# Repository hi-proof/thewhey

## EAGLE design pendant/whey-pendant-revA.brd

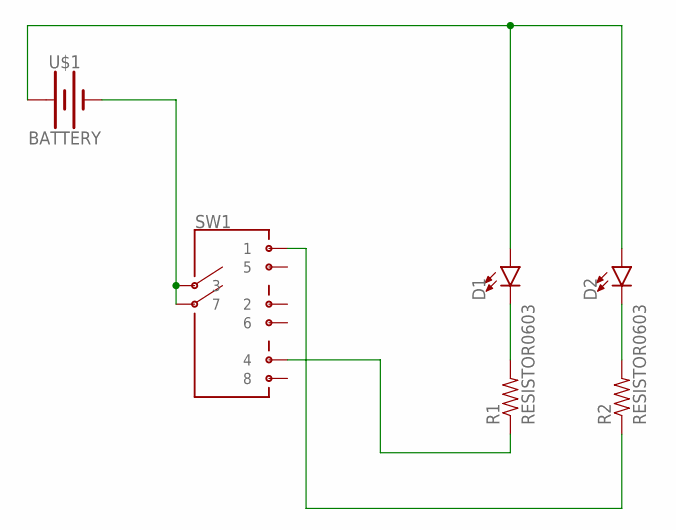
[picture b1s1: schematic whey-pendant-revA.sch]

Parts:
D1, D2: LED1206; LED-1206
R1, R2: RESISTOR0603; R0603
SW1: JS203011JCQN
U$1: BATTERY; COINCELL16

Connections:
unnamed: D1.A, D2.A, U$1.P$1 (+), U$1.P$2 (+)
unnamed: D1.C, R1.2
unnamed: D2.C, R2.2
unnamed: SW1.3, SW1.7, U$1.P$3 (-)
unnamed: R1.1, SW1.4
unnamed: R2.1, SW1.1

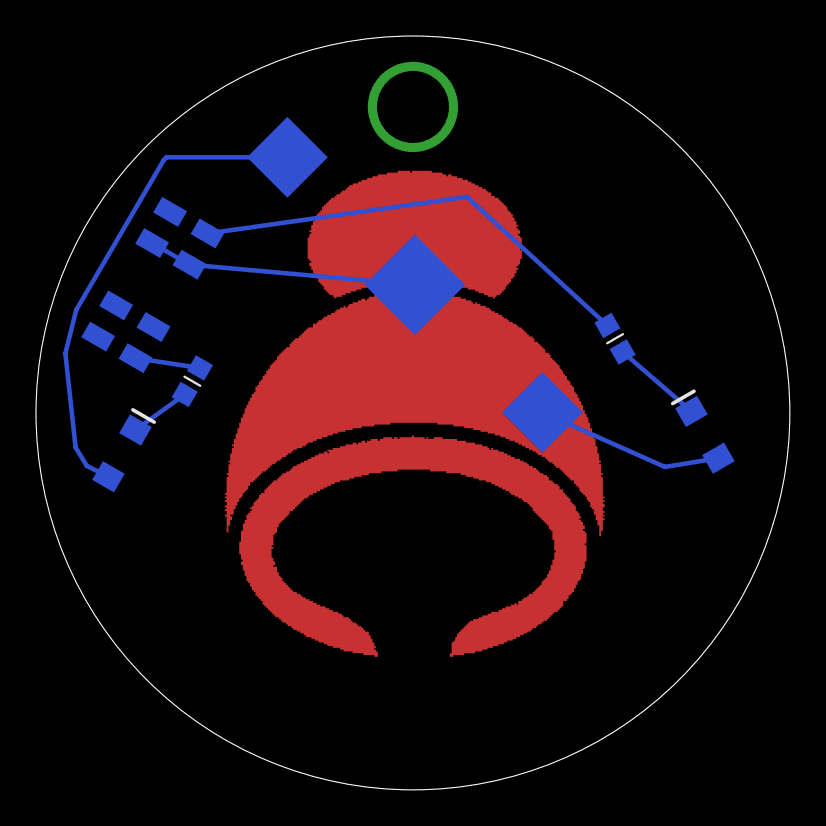
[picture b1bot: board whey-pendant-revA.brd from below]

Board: 2 copper layers, 41.9 x 41.9 mm, 6 parts (6 on the bottom side), 6 nets.

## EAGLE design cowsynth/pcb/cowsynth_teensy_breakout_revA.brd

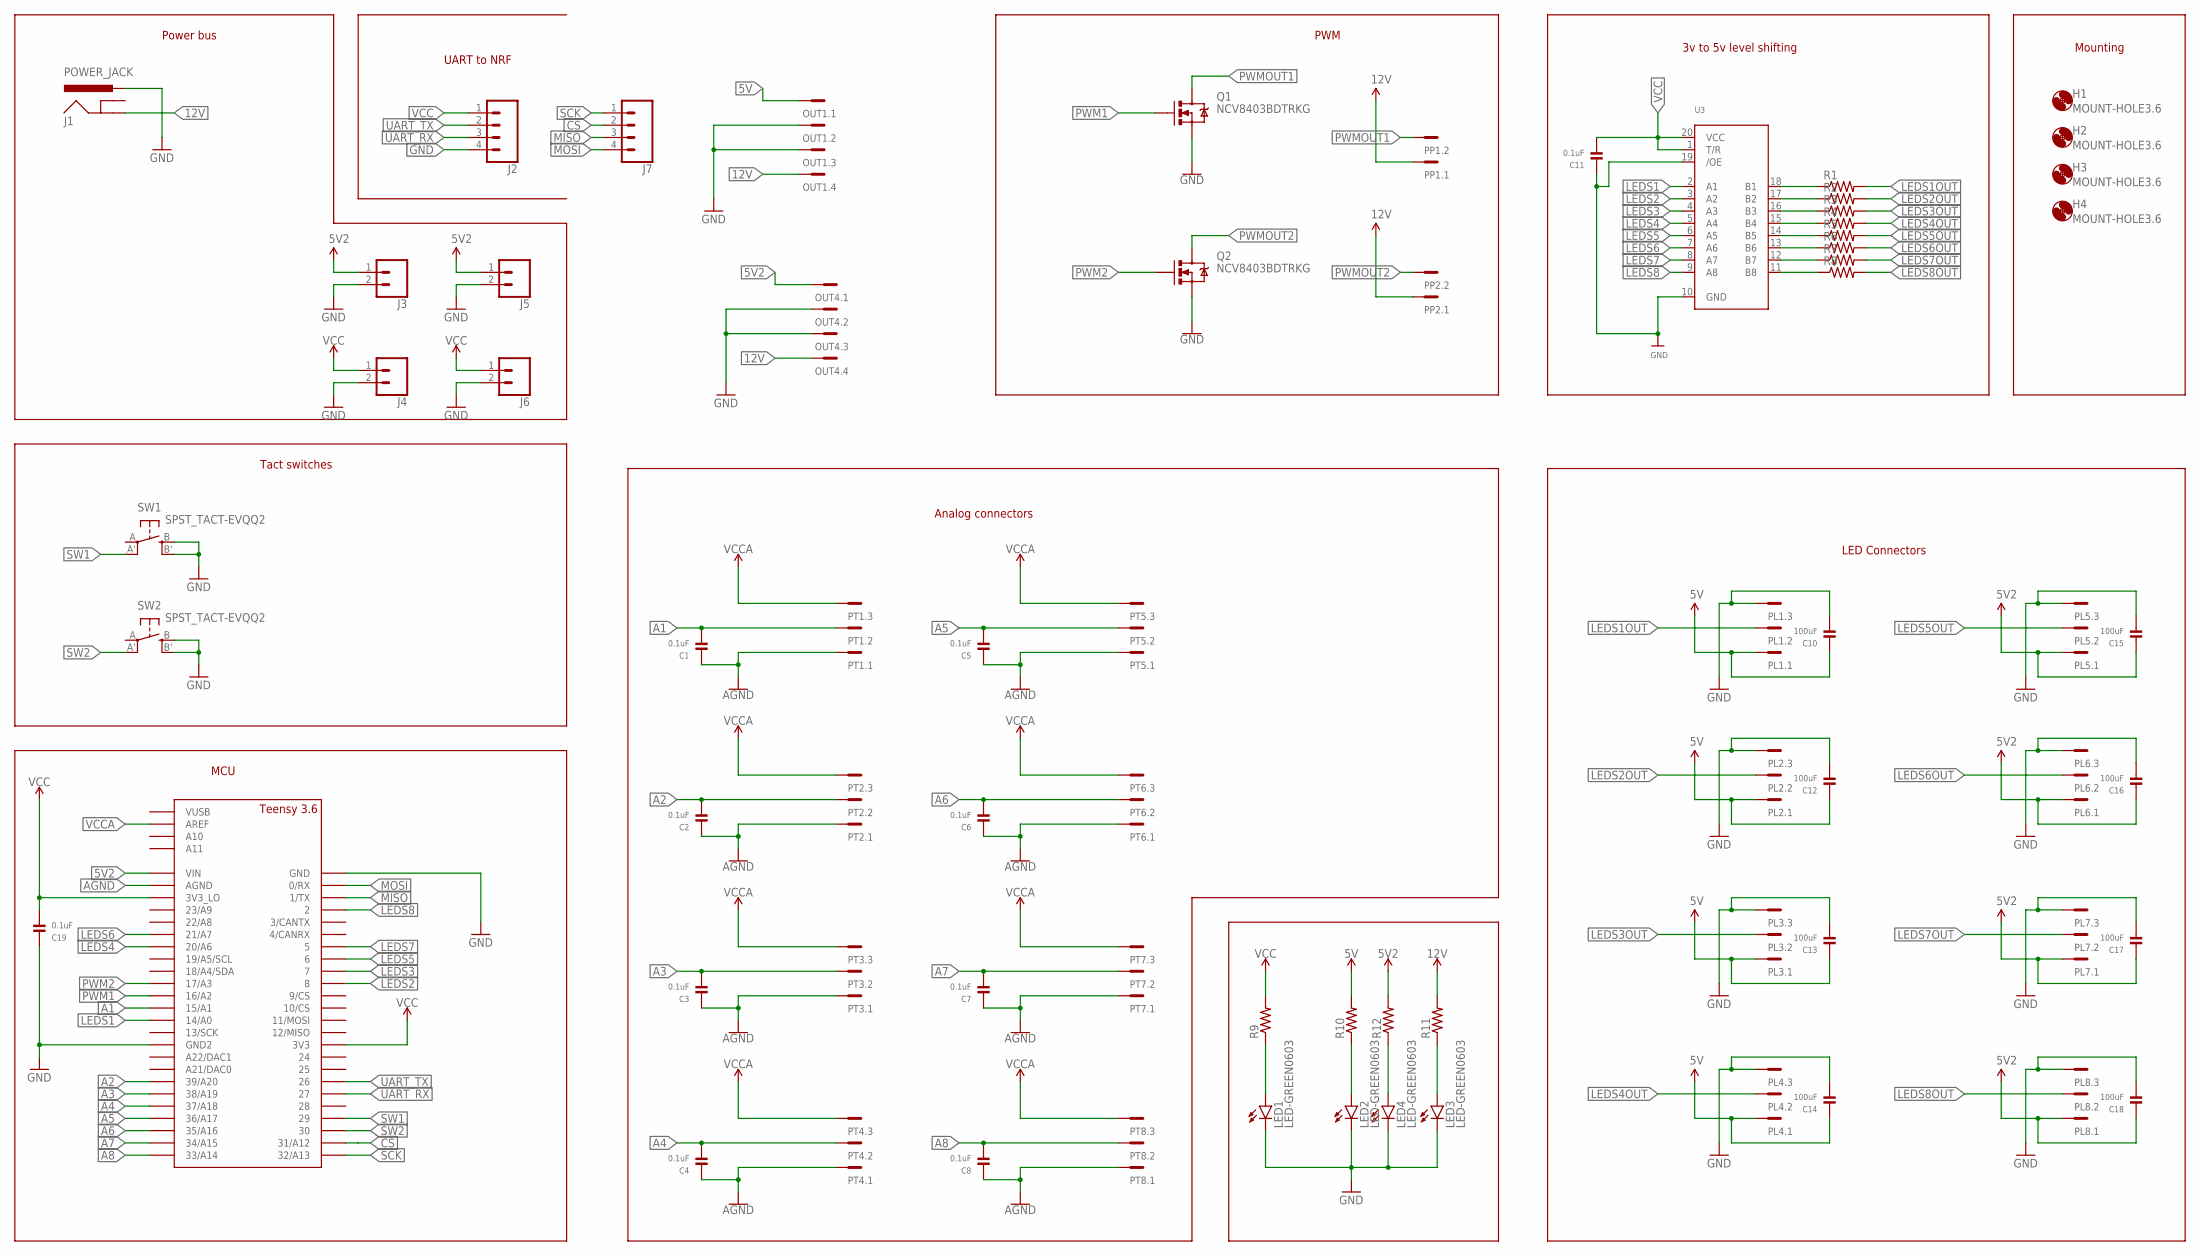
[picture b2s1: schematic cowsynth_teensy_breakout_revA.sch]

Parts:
C1, C2, C3, C4, C5, C6, C7, C8, C11, C19: 0.1uF; 0603
C10, C12, C13, C14, C15, C16, C17, C18: 100uF; 1206
H1, H2, H3, H4: MOUNT-HOLE3.6; 3,6
J1: POWER_JACK; POWER_JACK_PTH
J2, J7: CONN_04; 1X04
J3, J4, J5, J6: CONN_02; 1X02
LED1, LED2, LED3, LED4: LED-GREEN0603; 0603-GREEN
OUT1, OUT4: MC4
PL1, PL2, PL3, PL4, PL5, PL6, PL7, PL8: MC3
PP1, PP2: MC2
PT1, PT2, PT3, PT4, PT5, PT6, PT7, PT8: MC3
Q1, Q2: NCV8403BDTRKG; DPAK
R1, R2, R3, R4, R5, R6, R7, R8, R9, R10, R11, R12: R-US_R0603; R0603
SW1, SW2: SPST_TACT-EVQQ2; EVQ-Q2
U3: 74LCX245; TSSOP20
U$1: TEENSY_3.5/3.6_BASIC

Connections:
5V: C10.1, C12.1, C13.1, C14.1, OUT1.1, PL1.1, PL2.1, PL3.1, PL4.1, R10.2
5V2: C15.1, C16.1, C17.1, C18.1, J3.1, J5.1, OUT4.1, PL5.1, PL6.1, PL7.1, PL8.1, R12.2, U$1.VIN
12V: J1.GND, OUT1.4, OUT4.4, PP1.1, PP2.1, R11.2
A1: C1.2, PT1.2, U$1.15/A1
A2: C2.2, PT2.2, U$1.39/A20
A3: C3.2, PT3.2, U$1.38/A19
A4: C4.2, PT4.2, U$1.37/A18
A5: C5.2, PT5.2, U$1.36/A17
A6: C6.2, PT6.2, U$1.35/A16
A7: C7.2, PT7.2, U$1.34/A15
A8: C8.2, PT8.2, U$1.33/A14
AGND: C1.1, C2.1, C3.1, C4.1, C5.1, C6.1, C7.1, C8.1, PT1.1, PT2.1, PT3.1, PT4.1, PT5.1, PT6.1, PT7.1, PT8.1, U$1.AGND
CS: J7.2, U$1.31/A12
GND: C10.2, C11.1, C12.2, C13.2, C14.2, C15.2, C16.2, C17.2, C18.2, C19.1, J1.PWR, J2.4, J3.2, J4.2, J5.2, J6.2, LED1.C, LED2.C, LED3.C, LED4.C, OUT1.2, OUT1.3, OUT4.2, OUT4.3, PL1.3, PL2.3, PL3.3, PL4.3, PL5.3, PL6.3, PL7.3, PL8.3, Q1.3 (S), Q2.3 (S), SW1.B (S), SW1.B' (S1), SW2.B (S), SW2.B' (S1), U3.10 (GND), U3.19 (/OE), U$1.GND, U$1.GND2
LEDS1: U3.2 (A1), U$1.14/A0
LEDS1OUT: PL1.2, R1.2
LEDS2: U3.3 (A2), U$1.8
LEDS2OUT: PL2.2, R2.2
LEDS3: U3.4 (A3), U$1.7
LEDS3OUT: PL3.2, R3.2
LEDS4: U3.5 (A4), U$1.20/A6
LEDS4OUT: PL4.2, R4.2
LEDS5: U3.6 (A5), U$1.6
LEDS5OUT: PL5.2, R5.2
LEDS6: U3.7 (A6), U$1.21/A7
LEDS6OUT: PL6.2, R6.2
LEDS7: U3.8 (A7), U$1.5
LEDS7OUT: PL7.2, R7.2
LEDS8: U3.9 (A8), U$1.2
LEDS8OUT: PL8.2, R8.2
MISO: J7.3, U$1.1/TX
MOSI: J7.4, U$1.0/RX
unnamed: LED4.A, R12.1
unnamed: LED1.A, R9.1
unnamed: LED2.A, R10.1
unnamed: LED3.A, R11.1
unnamed: R1.1, U3.18 (B1)
unnamed: R2.1, U3.17 (B2)
unnamed: R3.1, U3.16 (B3)
unnamed: R4.1, U3.15 (B4)
unnamed: R5.1, U3.14 (B5)
unnamed: R6.1, U3.13 (B6)
unnamed: R7.1, U3.12 (B7)
unnamed: R8.1, U3.11 (B8)
PWM1: Q1.1 (G), U$1.16/A2
PWM2: Q2.1 (G), U$1.17/A3
PWMOUT1: PP1.2, Q1.4 (D)
PWMOUT2: PP2.2, Q2.4 (D)
SCK: J7.1, U$1.32/A13
SW1: SW1.A' (P1), U$1.29
SW2: SW2.A' (P1), U$1.30
UART_RX: J2.3, U$1.27
UART_TX: J2.2, U$1.26
VCC: C11.2, C19.2, J2.1, J4.1, J6.1, R9.2, U3.1 (T/R), U3.20 (VCC), U$1.3V3, U$1.3V3_LO
VCCA: PT1.3, PT2.3, PT3.3, PT4.3, PT5.3, PT6.3, PT7.3, PT8.3, U$1.AREF

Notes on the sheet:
3v to 5v level shifting
Power bus
MCU
Analog connectors
PWM
LED Connectors
UART to NRF
Tact switches
Mounting

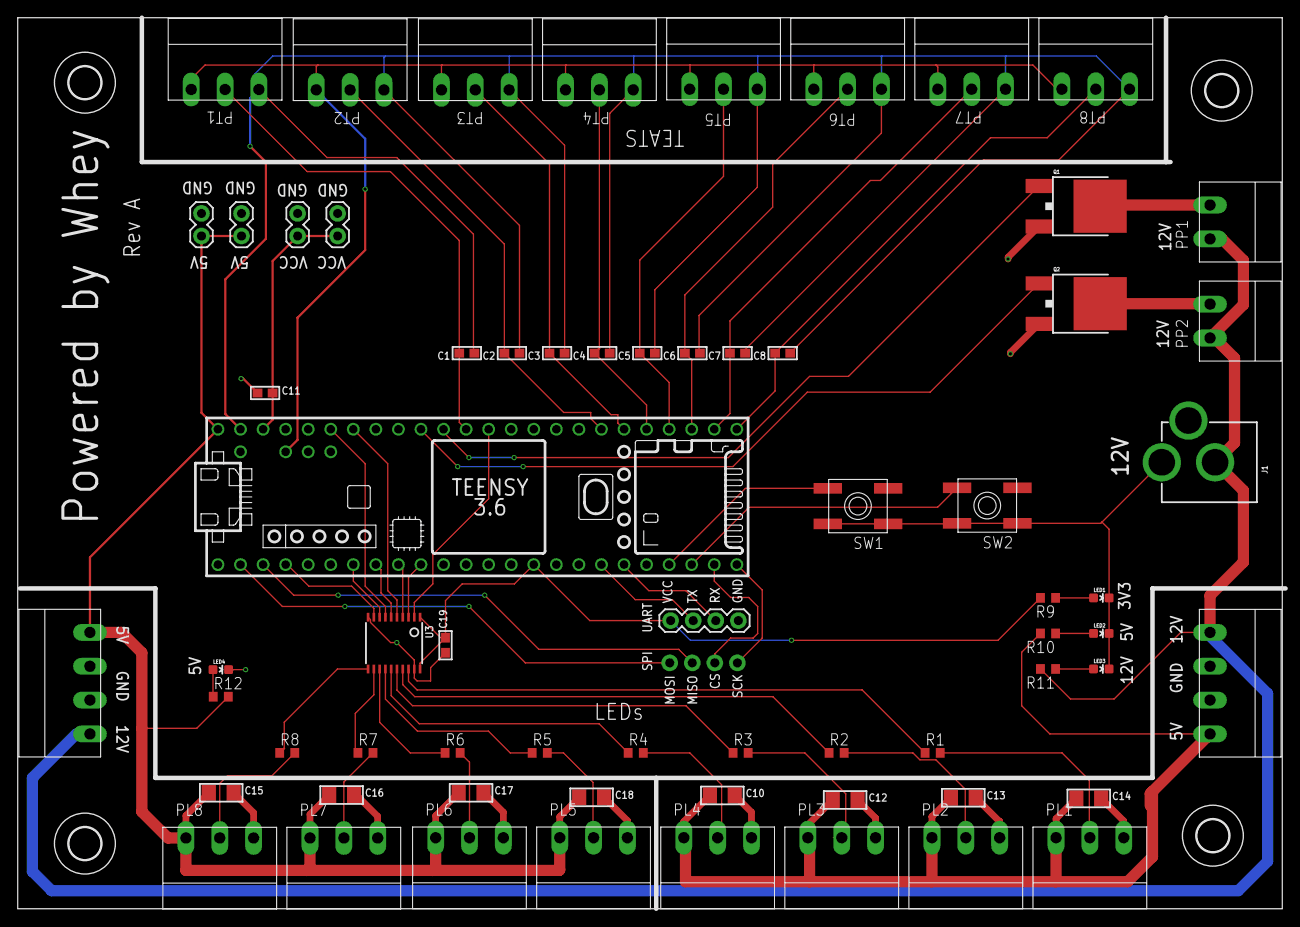
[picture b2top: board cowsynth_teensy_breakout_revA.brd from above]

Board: 2 copper layers, 142.4 x 100.3 mm, 71 parts (1 on the bottom side), 55 nets.

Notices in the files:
parts and their libraries:
microbuilder: This work is placed in the public domain, and may be freely used for commercial and non-commercial work with the following conditions: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
SparkFun-Connectors: Licensing: Creative Commons ShareAlike 4.0 International - https://creativecommons.org/licenses/by-sa/4.0
